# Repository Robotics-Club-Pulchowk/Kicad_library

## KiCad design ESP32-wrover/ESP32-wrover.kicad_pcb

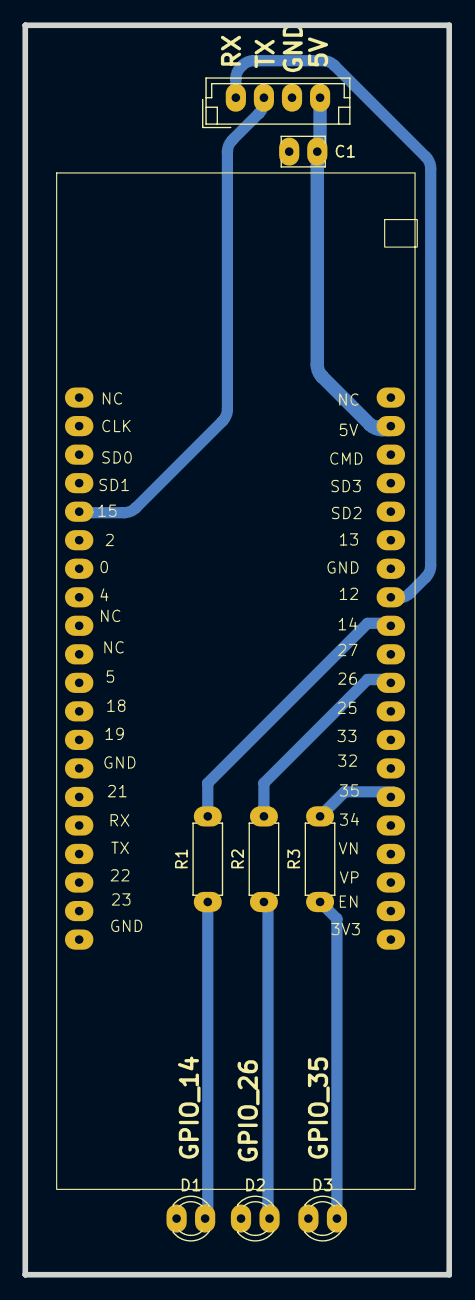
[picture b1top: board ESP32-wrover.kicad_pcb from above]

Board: 2 copper layers, 37.8 x 111.2 mm, 9 parts (0 on the bottom side), 10 nets.

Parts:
C1: C; Capacitor_Disc_Small
D1, D2, D3: LED; LED_D3.0mm
ESP32T1: ESP32_T18 - 3.0; ESP32_T18-3.0
J1: Conn_01x04_Pin; jst_4
R1, R2, R3: R; Resistor_small

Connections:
+5V: C1.1, ESP32T1.5V (CMD), J1.4
/1: D1.2 (A), R1.1
/2: D2.2 (A), R2.1
/3: D3.2 (A), R3.1
/LED1: ESP32T1.14 (GND), R1.2
/LED2: ESP32T1.26 (33), R2.2
/LED3: ESP32T1.35 (22), R3.2
/RX: ESP32T1.15 (4), J1.2
/TX: ESP32T1.12 (13), J1.1
GND: C1.2, D1.1 (K), D2.1 (K), D3.1 (K), ESP32T1.GND (SD3), J1.3

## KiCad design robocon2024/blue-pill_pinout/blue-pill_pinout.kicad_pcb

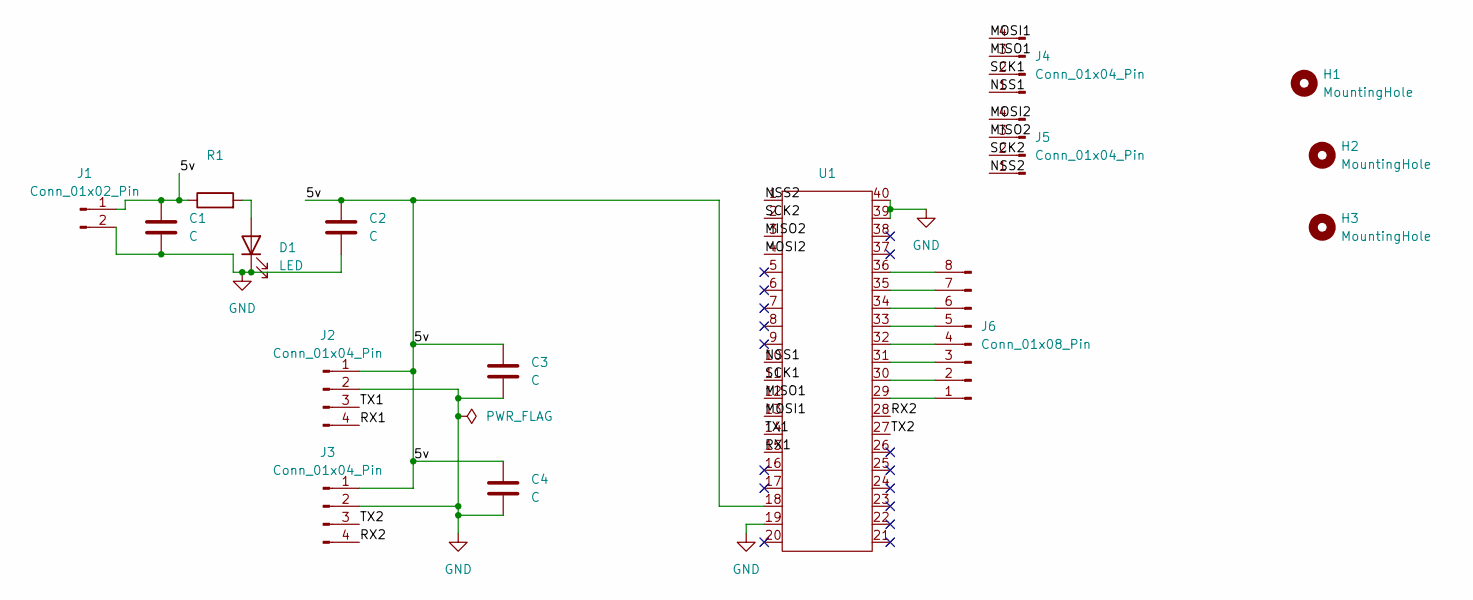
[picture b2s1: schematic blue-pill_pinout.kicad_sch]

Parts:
C1: C; Capacitor_10uF
C2, C3, C4: C; Capacitor_Disc_Small
D1: LED; LED_D3.0mm
H1, H2, H3: MountingHole; MountingHole_3mm
J1: Conn_01x02_Pin; bornier2
J2, J3, J4, J5: Conn_01x04_Pin; jst_4
J6: Conn_01x08_Pin; conn_1x08
R1: R; Resistor_small
U1: bluepill

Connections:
/5v: C1.1, C2.1, C3.1, C4.1, J1.1, J2.1, J3.1, R1.1, U1.18
/MISO1: J4.3, U1.12
/MISO2: J5.3, U1.3
/MOSI1: J4.4, U1.13
/MOSI2: J5.4, U1.4
/NSS1: J4.1, U1.10
/NSS2: J5.1, U1.1
/RX1: J2.4, U1.15
/RX2: J3.4, U1.28
/SCK1: J4.2, U1.11
/SCK2: J5.2, U1.2
/TX1: J2.3, U1.14
/TX2: J3.3, U1.27
GND: C1.2, C2.2, C3.2, C4.2, D1.1 (K), J1.2, J2.2, J3.2, U1.19, U1.39, U1.40
unnamed: D1.2 (A), R1.2
unnamed: J6.1, U1.29
unnamed: J6.2, U1.30
unnamed: J6.3, U1.31
unnamed: J6.4, U1.32
unnamed: J6.5, U1.33
unnamed: J6.6, U1.34
unnamed: J6.7, U1.35
unnamed: J6.8, U1.36

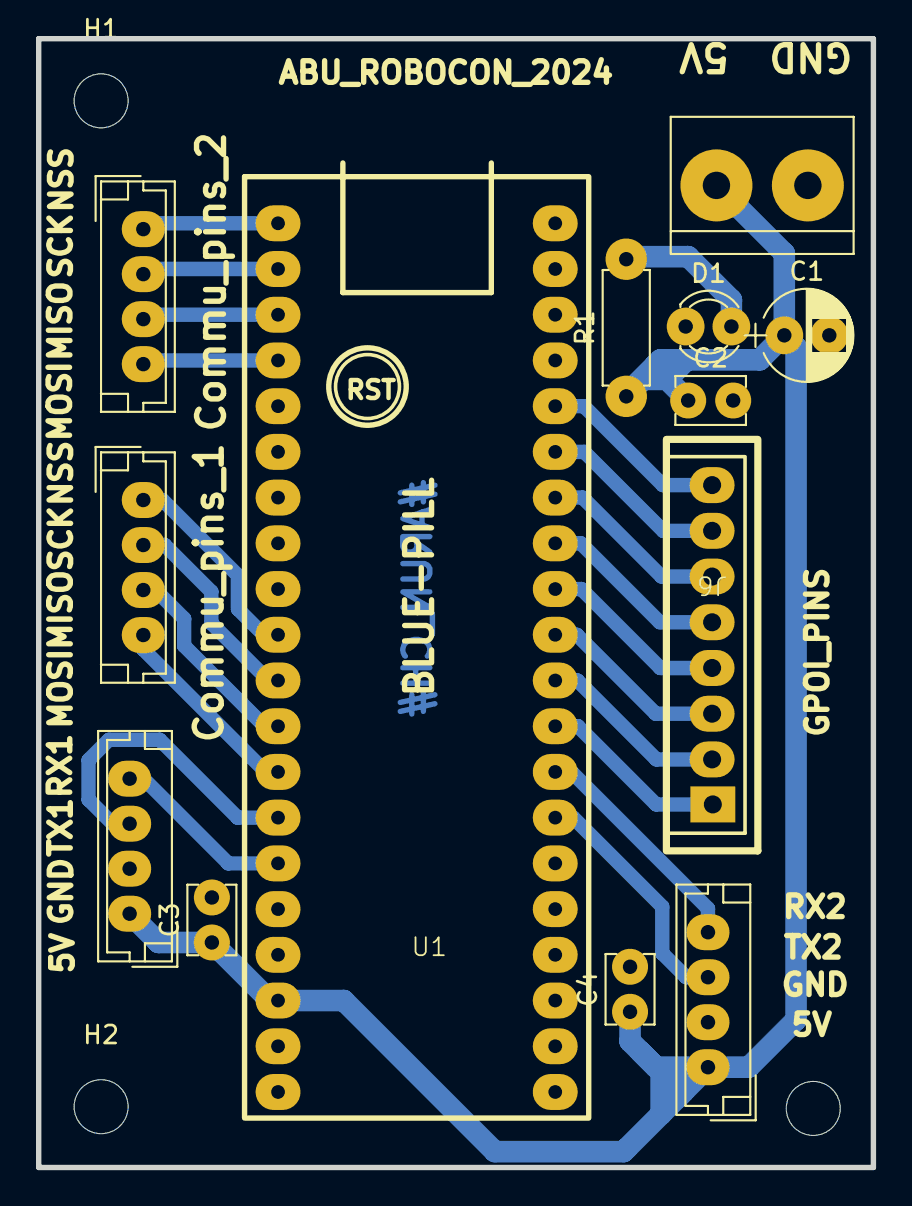
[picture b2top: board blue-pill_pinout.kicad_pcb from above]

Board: 2 copper layers, 46.4 x 62.7 mm, 16 parts (0 on the bottom side), 23 nets.

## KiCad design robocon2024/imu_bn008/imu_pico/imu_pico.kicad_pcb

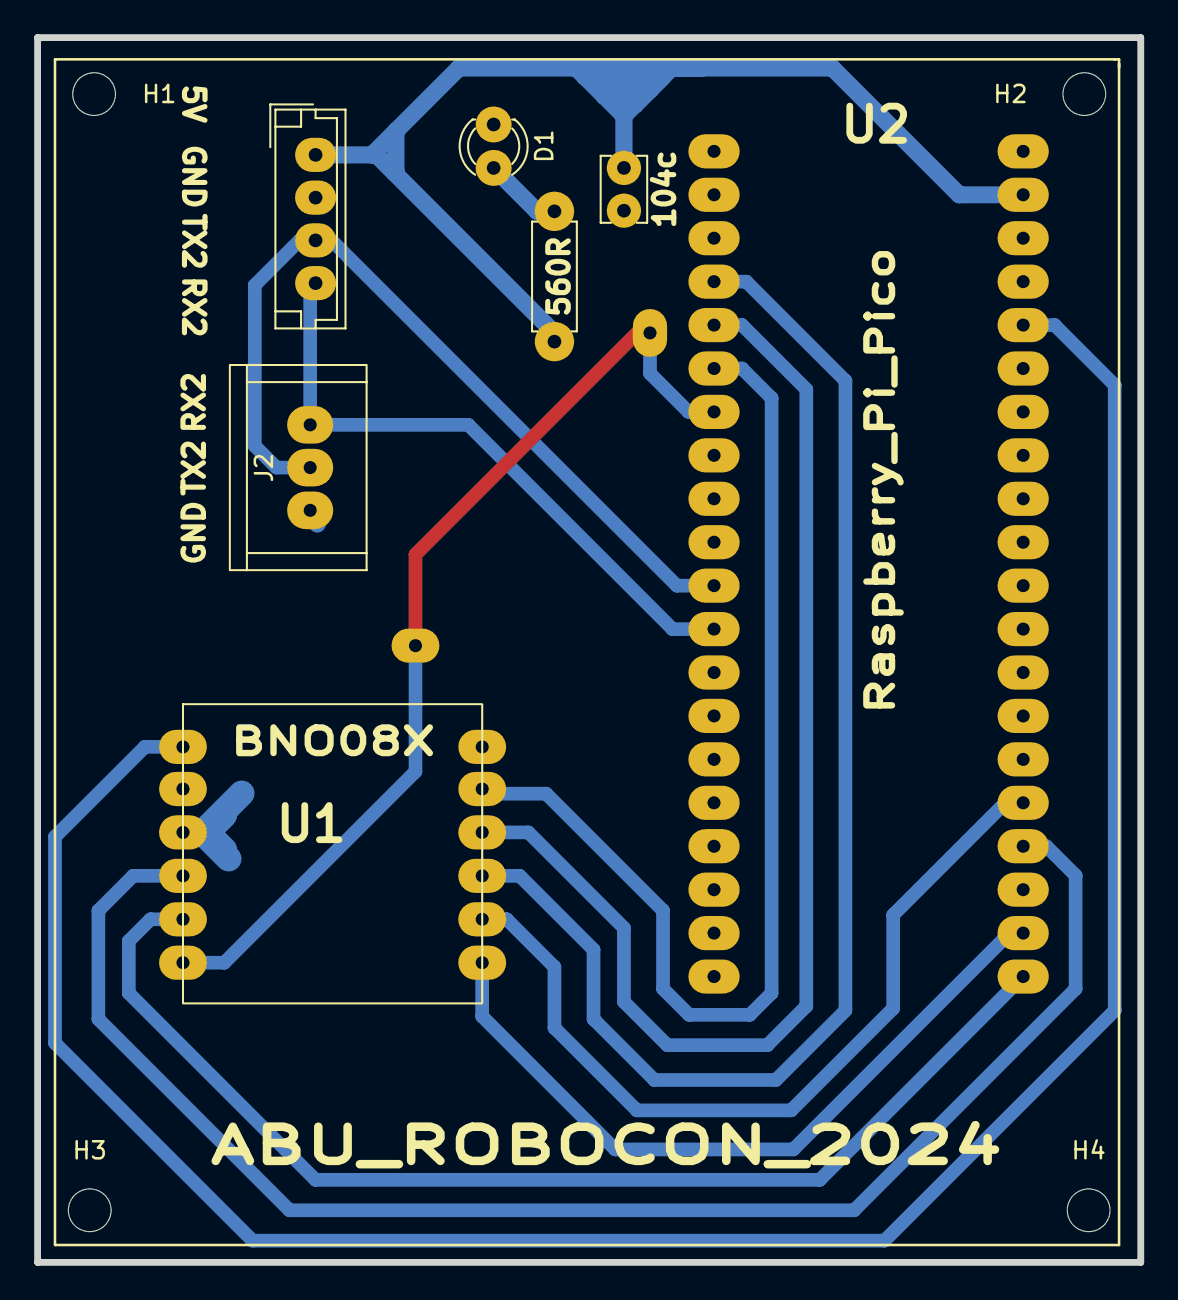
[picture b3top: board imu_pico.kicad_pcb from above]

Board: 2 copper layers, 64.5 x 71.6 mm, 11 parts (0 on the bottom side), 14 nets.

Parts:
104c: C; Capacitor_Disc_Small
560R: R; Resistor_small
D1: LED; LED_D3.0mm
H1, H2, H3, H4: MountingHole; MountingHole_2.5mm
J1: Conn_01x04_Male; jst_4
J2: Conn_01x03_Male; 1X03
U1: BNO08X
U2: rasp_pi_pico; Rasp_pi_pico

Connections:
/CS: U1.12 (CS), U2.22 (GP21)
/DI: U1.11 (DI), U2.25 (GP24)
/INT: U1.6 (INT), U2.7 (GP6)
/P0: U1.8 (P0), U2.6 (GP5)
/P1: U1.9 (P1), U2.5 (GP4)
/RST: U1.10 (RST), U2.4 (GP3)
/RX2: J1.4, J2.3, U2.12 (GP11)
/SCL: U1.4 (SCL), U2.24 (GP23)
/SDA: U1.5 (SDA), U2.21 (GP20)
/TX2: J1.3, J2.2, U2.11 (GP10)
/VIN: U1.1 (VIN), U2.36 (GP35)
/VSYS: 104c.1, 560R.1, J1.1, U2.39 (GP38)
GND: 104c.2, D1.1 (K), J1.2, J2.1, U1.3 (GND), U2.3 (GP2)
unnamed: 560R.2, D1.2 (A)

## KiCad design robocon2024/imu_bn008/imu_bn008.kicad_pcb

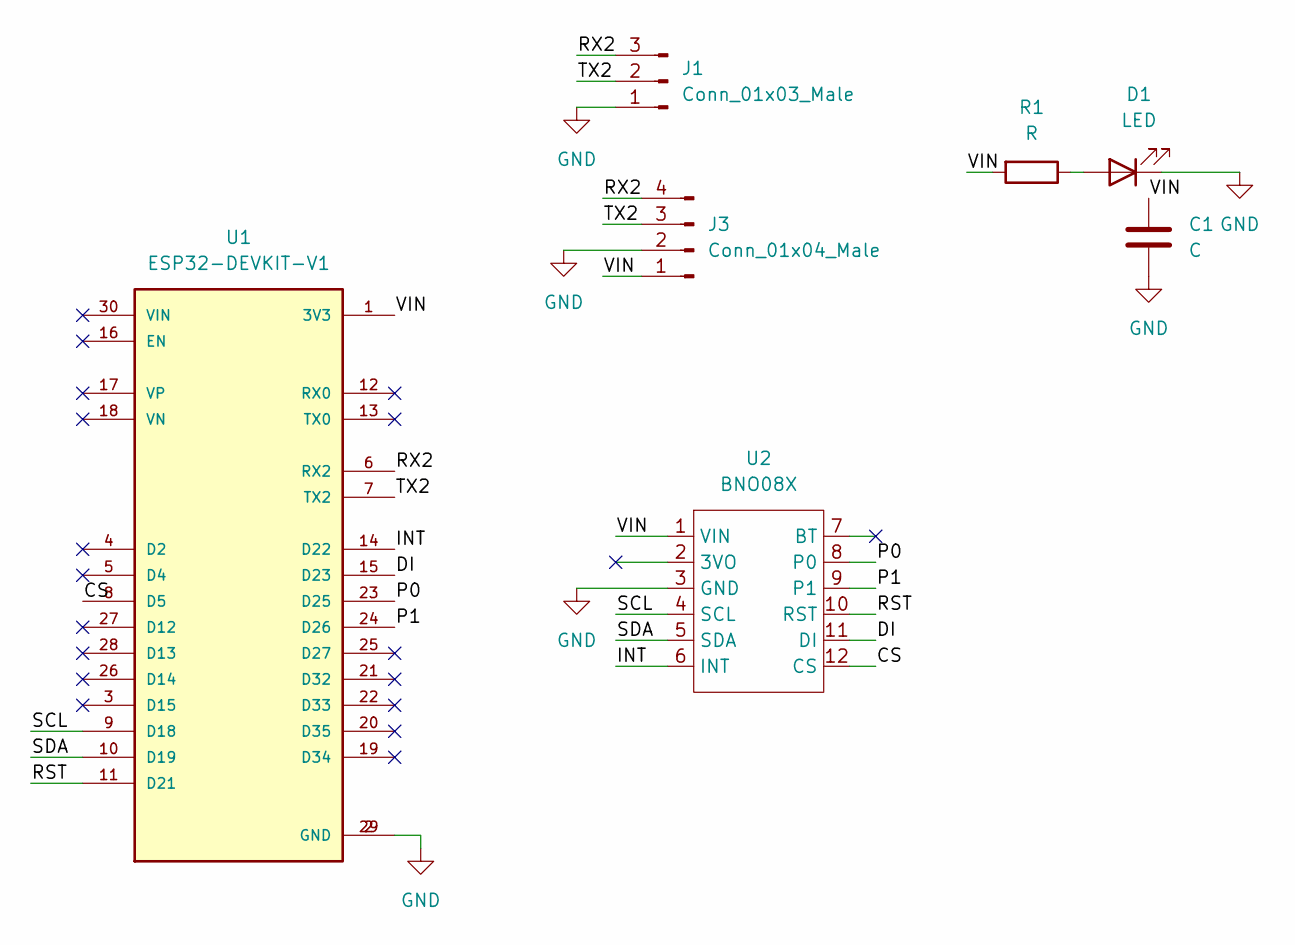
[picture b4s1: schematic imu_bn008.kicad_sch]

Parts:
C1: C; Capacitor_Disc_Small
D1: LED; LED_D3.0mm
J1: Conn_01x03_Male; PinHeader_1x03_P2.54mm_Vertical
J3: Conn_01x04_Male; jst_4
R1: R; Resistor_small
U1: ESP32-DEVKIT-V1; MODULE_ESP32_DEVKIT_V1; PARTREV N/A
U2: BNO08X

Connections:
/CS: U1.8 (D5), U2.12 (CS)
/DI: U1.15 (D23), U2.11 (DI)
/INT: U1.14 (D22), U2.6 (INT)
/P0: U1.23 (D25), U2.8 (P0)
/P1: U1.24 (D26), U2.9 (P1)
/RST: U1.11 (D21), U2.10 (RST)
/RX2: J1.3, J3.4, U1.6 (RX2)
/SCL: U1.9 (D18), U2.4 (SCL)
/SDA: U1.10 (D19), U2.5 (SDA)
/TX2: J1.2, J3.3, U1.7 (TX2)
/VIN: C1.1, J3.1, R1.2, U1.1 (3V3), U2.1 (VIN)
GND: C1.2, D1.1 (K), J1.1, J3.2, U1.2 (GND), U1.29 (GND), U2.3 (GND)
unnamed: D1.2 (A), R1.1

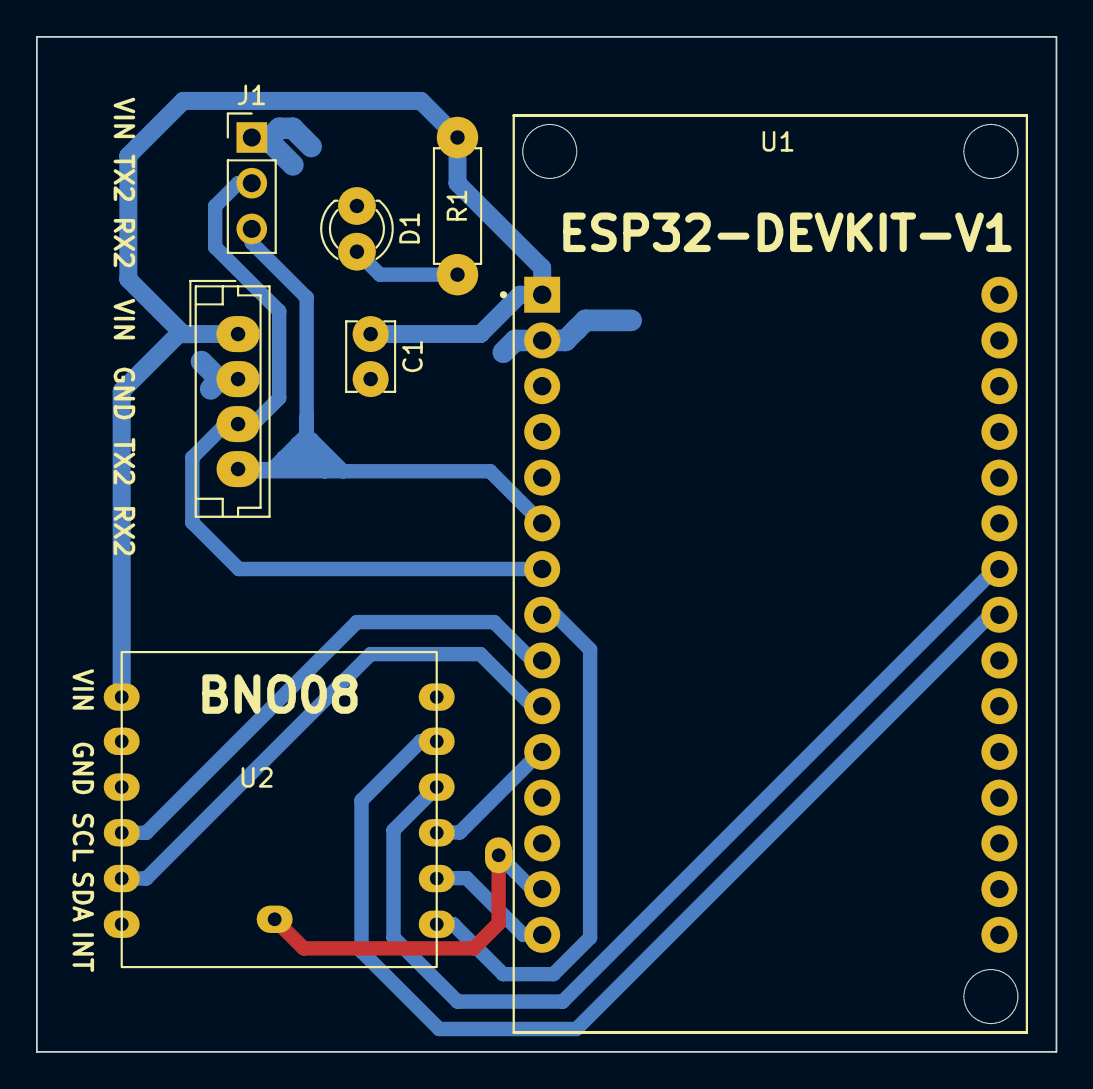
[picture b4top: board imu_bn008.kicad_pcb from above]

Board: 2 copper layers, 56.6 x 56.4 mm, 7 parts (0 on the bottom side), 13 nets.

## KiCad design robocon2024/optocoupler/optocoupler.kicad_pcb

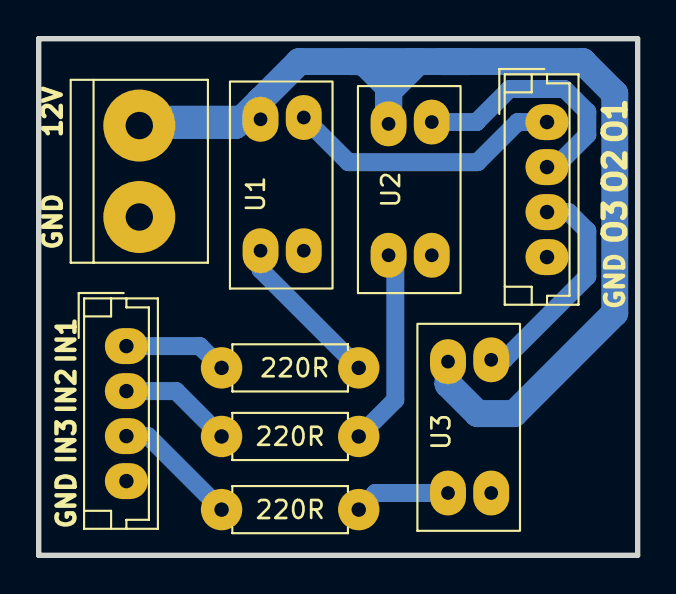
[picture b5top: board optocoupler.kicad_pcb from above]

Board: 2 copper layers, 33.3 x 28.7 mm, 9 parts (0 on the bottom side), 11 nets.

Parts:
220R, 220R#2, 220R#3: R; Resistor_small
J1, J2: Conn_01x04_Male; jst_4
J3: Conn_01x02_Male; bornier2
U1, U2, U3: NSL-32; U

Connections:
/12v: J3.1, U1.4 (R), U2.4 (R), U3.4 (R)
/numi1: 220R.2, U1.1 (A)
/numi2: 220R#3.2, U2.1 (A)
/numi3: 220R#2.2, U3.1 (A)
/numo1: J2.1, U1.3 (R)
/numo2: J2.2, U2.3 (R)
/numo3: J2.3, U3.3 (R)
GND: J1.4, J2.4, J3.2, U1.2 (K), U2.2 (K), U3.2 (K)
unnamed: 220R.1, J1.1
unnamed: 220R#3.1, J1.2
unnamed: 220R#2.1, J1.3

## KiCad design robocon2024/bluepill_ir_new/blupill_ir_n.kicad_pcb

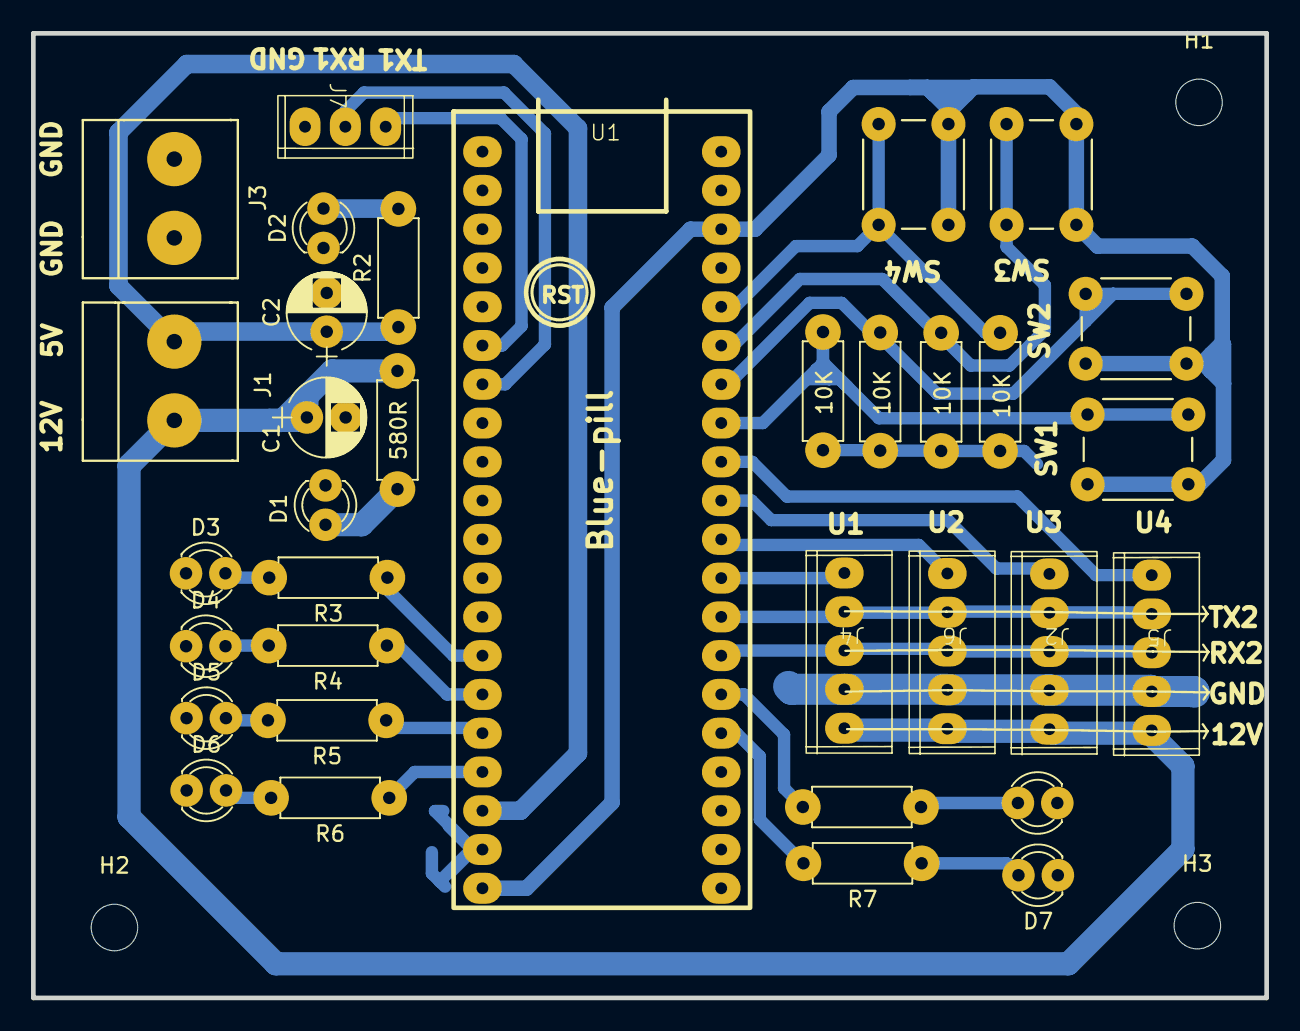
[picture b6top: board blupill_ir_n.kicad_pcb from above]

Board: 2 copper layers, 79.5 x 62.2 mm, 37 parts (0 on the bottom side), 30 nets.

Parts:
10K, 10K#2, 10K#3, 10K#4, 580R: R; Resistor_small
C1, C2: C; Capacitor_10uF
D1, D2, D3, D4, D5, D6, D7, D8: LED; LED_D3.0mm
H1, H2, H3: MountingHole; MountingHole_3mm
J1, J3: Conn_01x02_Pin; Connector_Bornier_2
J2, J4, J5, J6: Conn_01x05_Pin; jst_1x05
J7: Conn_01x03_Pin; jst_1x03
R2, R3, R4, R5, R6, R7, R8: R; Resistor_small
SW1, SW2, SW3, SW4: SW_Push; Push_Button
U1: bluepill

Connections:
/3.3V: SW1.2, SW2.2, SW3.2, SW4.2, U1.20, U1.38
/5V: C2.1, J1.2, R2.1, U1.18
/12V: 580R.1, C1.1, J1.1, J2.5, J4.5, J5.5, J6.5
/PA4: 10K#3.1, SW1.1, U1.33
/PA5: 10K.1, SW2.1, U1.34
/PA6: 10K#4.1, SW3.1, U1.35
/PA7: 10K#2.1, SW4.1, U1.36
/PB6: R3.1, U1.14
/PB7: R4.1, U1.15
/PB8: R5.1, U1.16
/PB9: R6.1, U1.17
/RX2: J2.3, J4.3, J5.3, J6.3, U1.27
/TX2: J2.2, J4.2, J5.2, J6.2, U1.28
/u1: J4.1, U1.29
/u2: J6.1, U1.30
/u3: J2.1, U1.31
/u4: J5.1, U1.32
GND: 10K.2, 10K#2.2, 10K#3.2, 10K#4.2, C1.2, C2.2, D1.1 (K), D2.1 (K), D3.1 (K), D4.1 (K), D5.1 (K), D6.1 (K), D7.1 (K), D8.1 (K), J2.4, J3.1, J3.2, J4.4, J5.4, J6.4, J7.3, U1.19, U1.39, U1.40
unnamed: 580R.2, D1.2 (A)
unnamed: D2.2 (A), R2.2
unnamed: D3.2 (A), R3.2
unnamed: D4.2 (A), R4.2
unnamed: D5.2 (A), R5.2
unnamed: D6.2 (A), R6.2
unnamed: D7.2 (A), R7.1
unnamed: D8.2 (A), R8.1
unnamed: J7.1, U1.6
unnamed: J7.2, U1.7
unnamed: R7.2, U1.25
unnamed: R8.2, U1.26

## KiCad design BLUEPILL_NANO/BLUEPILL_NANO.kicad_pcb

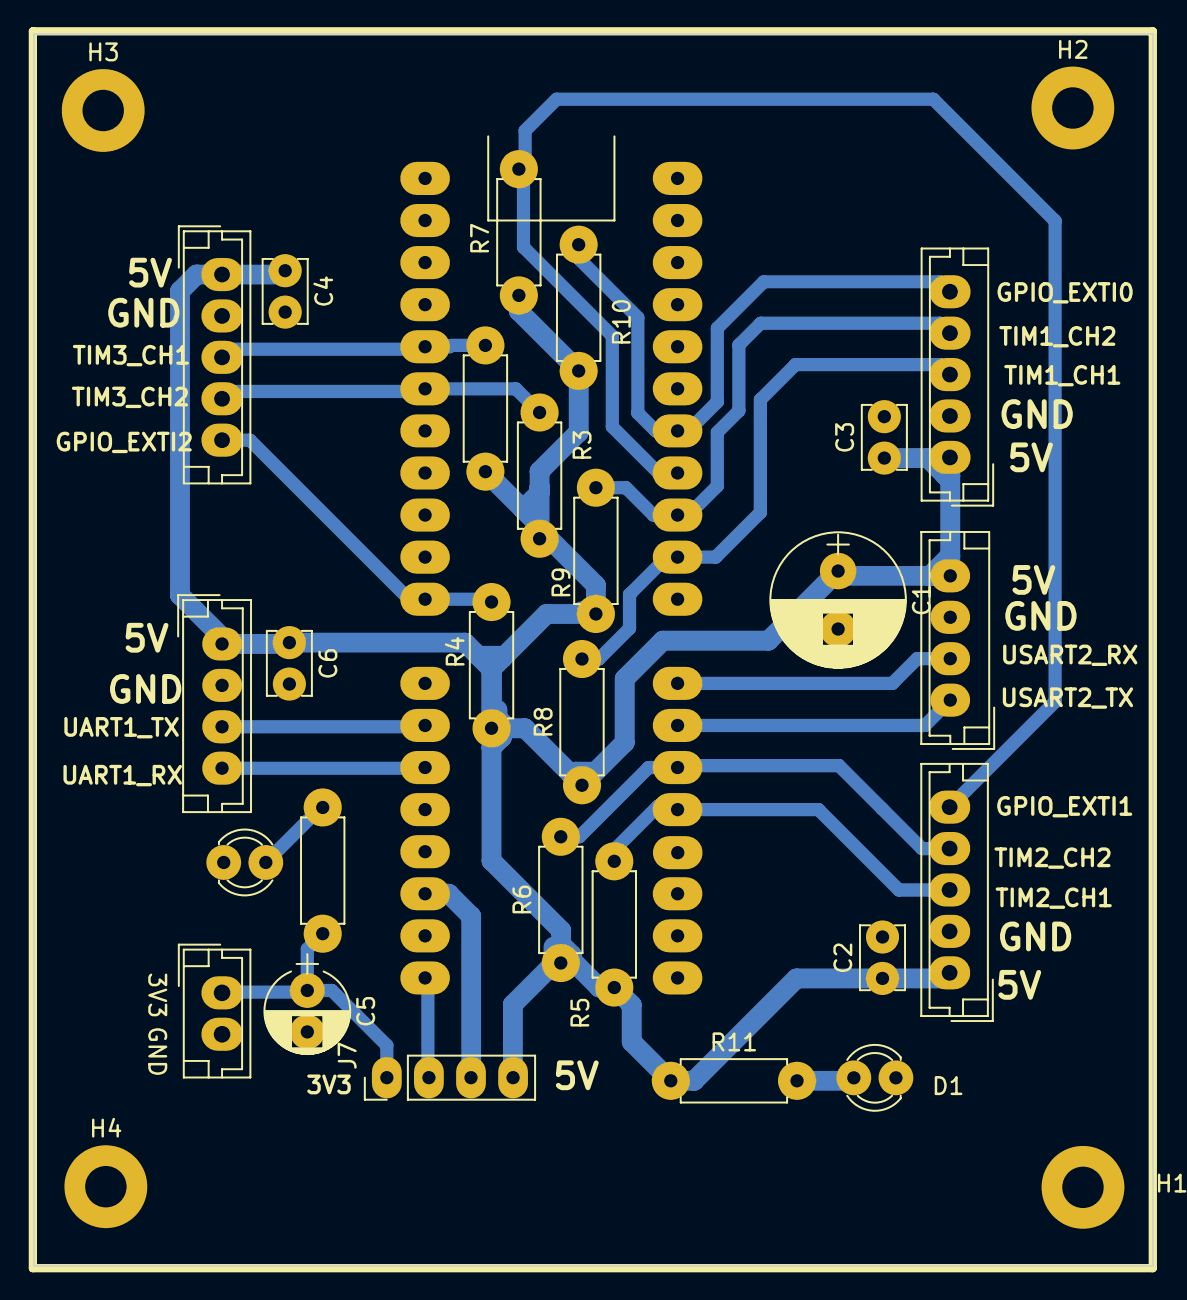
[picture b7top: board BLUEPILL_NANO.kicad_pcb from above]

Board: 2 copper layers, 67.5 x 74.4 mm, 31 parts (0 on the bottom side), 20 nets.

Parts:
C1: C; Capacitor_100uF
C2, C3, C4: C_Polarized_US; Capacitor_Disc_Small
C5: C; Capacitor_10uF
C6: C; Capacitor_Disc_Small
D1, D2: LED; LED_D3.0mm
H1, H2, H3, H4: MountingHole; MountingHole_2.5mm_Pad
J1, J2, J3: Conn_01x05; JST_EH_B5B-EH-A_1x05_P2.50mm_Vertical
J4: Conn_01x04_Pin; jst_4
J5: Conn_01x04; jst_4
J6: Conn_01x02_Pin; JST_EH_B2B-EH-A_1x02_P2.50mm_Vertical
J7: Conn_01x04; PinHeader_1x04_P2.54mm_Vertical
R1, R2, R3, R4, R5, R6, R7, R8, R9, R10, R11: R; Resistor_small
U2: BluePill; STM32_BLUEPLL_MOD

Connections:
+5V: C1.1, C2.1, C3.1, C4.1, C6.1, J1.1, J2.1, J3.1, J4.1, J5.4, J7.4, R1.1, R3.1, R4.1, R5.1, R6.1, R7.1, R8.1, R9.1, R10.1, R11.1
/3V3: C5.1, J6.1, J7.1, R2.1
/EXP0: J3.5, R10.2, U2.34 (PB1)
/EXP1: J2.5, R7.2, U2.33 (PB0)
/EXP2: J1.5, R4.2, U2.11 (PB3)
/UART_RX: J4.4, U2.15 (PB7)
/UART_TX: J4.3, U2.14 (PB6)
/USART2_RX: J5.2, U2.28 (PA3)
/USART2_TX: J5.1, U2.27 (PA2)
/VIN3: J7.2, U2.20 (3V3), U2.38 (3V3)
/Vin: J7.3, U2.18 (5V)
GND: C1.2, C2.2, C3.2, C4.2, C5.2, C6.2, D1.1 (K), D2.1 (K), J1.2, J2.2, J3.2, J4.2, J5.3, J6.2, U2.19 (GND), U2.39 (GND), U2.40 (GND)
unnamed: D1.2 (A), R11.2
unnamed: D2.2 (A), R2.2
unnamed: J1.3, R1.2, U2.5 (PA8)
unnamed: J1.4, R3.2, U2.6 (PA9)
unnamed: J2.3, R5.2, U2.25 (PA0)
unnamed: J2.4, R6.2, U2.26 (PA1)
unnamed: J3.3, R8.2, U2.31 (PA6)
unnamed: J3.4, R9.2, U2.32 (PA7)

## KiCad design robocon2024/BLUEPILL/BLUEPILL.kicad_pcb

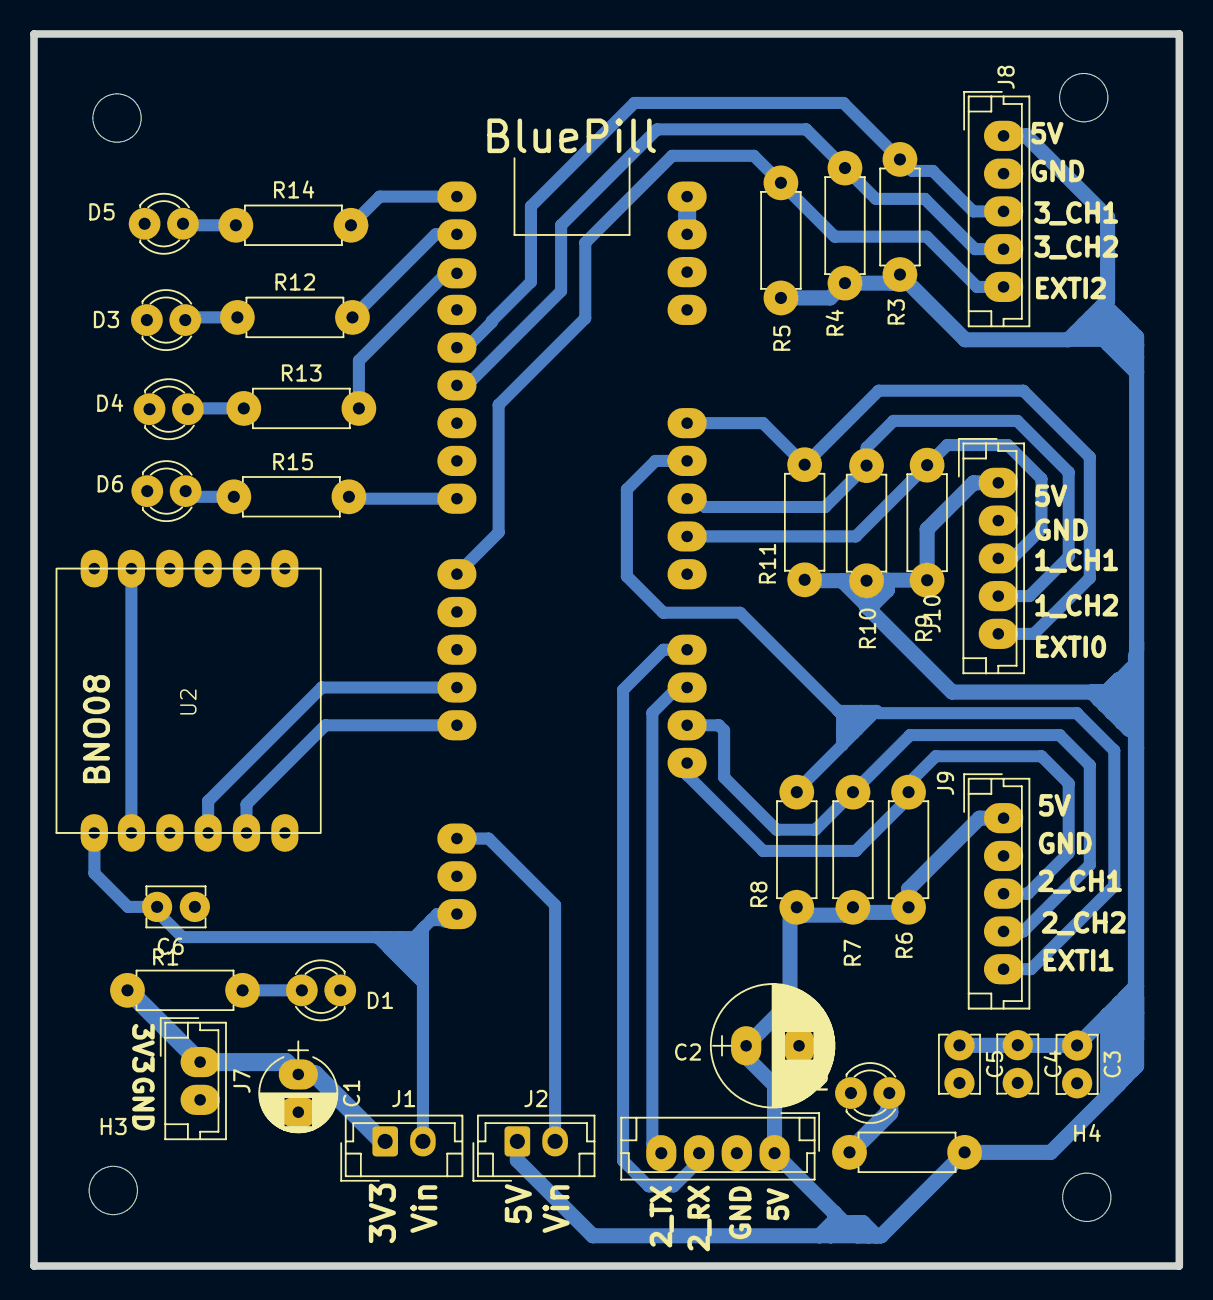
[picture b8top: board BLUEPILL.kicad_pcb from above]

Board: 2 copper layers, 75.8 x 81.6 mm, 40 parts (0 on the bottom side), 29 nets.

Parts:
C1: C; Capacitor_10uF
C2: C; Capacitor_100uF
C3, C4, C5, C6: C; Capacitor_Disc_Small
D1, D2, D3, D4, D5, D6: LED; LED_D3.0mm
H1, H2, H3, H4: MountingHole; MountingHole_3.2mm_M3
J1, J2, J7: Conn_01x02_Pin; JST_EH_B2B-EH-A_1x02_P2.50mm_Vertical
J6: Conn_01x04_Pin; jst_4
J8, J9, J10: Conn_01x05_Pin; JST_EH_B5B-EH-A_1x05_P2.50mm_Vertical
R1, R2, R3, R4, R5, R6, R7, R8, R9, R10, R11, R12, R13, R14, R15: R; Resistor_small
U1: BluePill; STM32_BLUEPLL_MOD
U2: bno08

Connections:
/1: D5.2 (A), R14.1
/2: D4.2 (A), R13.1
/3: D3.2 (A), R12.1
/3V0: U2.2 (3V0), U2.8 (PO)
/3V3: C1.1, J1.1, J7.1, R1.2
/4: D6.2 (A), R15.1
/5V: C2.1, C3.1, C4.1, C5.1, J2.1, J6.1, J8.1, J9.1, J10.1, R2.2, R3.1, R4.1, R5.1, R6.1, R7.1, R8.1, R9.1, R10.1, R11.1
/E: D2.2 (A), R2.1
/EXTI0: J10.5, R11.2, U1.34 (PB1)
/EXTI1: J9.5, R8.2, U1.33 (PB0)
/EXTI2: J8.5, R5.2, U1.11 (PB3)
/L: D1.2 (A), R1.1
/LED_1: R14.2, U1.1 (PB12)
/LED_2: R13.2, U1.3 (PB14)
/LED_3: R12.2, U1.2 (PB13)
/LED_4: R15.2, U1.9 (PA12)
/TIM1_CH2: J8.4, R4.2, U1.6 (PA9)
/TIM2_CH1: J9.3, R6.2, U1.25 (PA0)
/TIM2_CH2: J9.4, R7.2, U1.26 (PA1)
/TIM_CH2: J10.4, R10.2, U1.32 (PA7)
/TM1_CH1: J8.3, R3.2, U1.5 (PA8)
/TM3_CH1: J10.3, R9.2, U1.31 (PA6)
/UART1_RX: U1.15 (PB7), U2.5 (SDA)
/UART1_TX: U1.14 (PB6), U2.4 (SCL)
/UART2_RX: J6.3, U1.28 (PA3)
/UART2_TX: J6.4, U1.27 (PA2)
/VIN3: C6.1, J1.2, U1.20 (3V3), U1.38 (3V3), U2.1 (VIN)
/VIN5: J2.2, U1.18 (5V)
GND: C1.2, C2.2, C3.2, C4.2, C5.2, C6.2, D1.1 (K), D2.1 (K), D3.1 (K), D4.1 (K), D5.1 (K), D6.1 (K), J6.2, J7.2, J8.2, J9.2, J10.2, U1.19 (GND), U1.39 (GND), U1.40 (GND), U2.3 (GND), U2.9 (P1)

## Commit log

2024-04-12 added bn008x symbol and footprint
2024-05-01 added bluepill ir circuit new design
2024-05-01 add optocoupler circuit: PC817
2024-05-01 added imu bno008
2024-05-04 bluepill bno08
2024-05-04 moved bluepill to robocon folder
2024-05-18 arduino motor circuit added
2024-05-18 blue-pill simple circuit added
2024-05-18 simple pinout ESP32 circuit added
2024-05-18 esp32 pinout circuit added
2024-05-18 bno08 symbols add
2024-05-18 MYLIB.pretty file updated
2024-06-06 mylib.pretty file is updated
2024-07-07 base circuit of 2024
2024-07-18 new compact base circuit 2024 is addede
2024-08-02 ESP32-t18 footprint and symbol
2024-08-03 new footprint
2025-01-01 add footprint
2025-01-09 update and add footprint
    added footprint for ams1117 module and updated buck footprint
2025-01-10 update footprint
2025-02-17 change in footprint
2025-04-24 jst modify
2025-04-26 edit the foorprint
2025-04-28 modify the foorprint
2025-05-10 Add files via upload
    added the footprint of the logo of the robotics club pulchowk
2025-05-10 Add files via upload
    add the logo only
2025-05-30 XT90 Vertical Footprint
2025-05-30 added latch switch and pot footprint
2025-05-30 change the footprint
2025-06-02 foorprint edit
2025-06-04 add the footprint
2025-06-04 add the footprint of pot
2025-06-10 added the footprint
2025-06-10 added footprint
2025-06-10 footprint
2025-06-11 added esp footprint
2025-06-21 addedd the footprint
